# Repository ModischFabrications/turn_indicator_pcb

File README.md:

# turn_indicator_pcb

This is the PCB for [Turn Indicator](https://github.com/ModischFabrications/Turn_Indicator).

Open like regular in KiCad. Look into the docs zip under [Actions/KiCad Exports](https://github.com/ModischFabrications/turn_indicator_pcb/actions/workflows/exports.yml) to see renderings. 

This schematic is meant to be soldered manually onto a perfboard, but feel free to order a PCB instead. 

## Decisions

Size is determined by a generic 4x6 cm perfboard. 

### Electrical
Button panel connectors are grouped in pairs of 4 because my JST-XH set only has 2..5 pins. 
Grouping by input/output was the obvious choice,even if they are crossed at the buttons. 

Supply is a 18650 in a supply board, which means that grounding is useless. Using the bicylce frame as common ground could have been simple, but it's not worth the risk if there are 4+ wires routed anyways. 

Short-circuit-resistance of the power leads is archieved using a polyfuse. Resistance of the inputs is build-in, as they are high impedance, but the outputs are at risk. 

Introducing series resistances into every single connection could have made it safer, but I can't be arsed at the moment. Active-Low or High doesn't really matter either, a cross between adjacent leads would result in one overloading regardless. Feel free to insert ~300 ohm everywhere if you want to be safe. 

Sharing Clocks for the LED-stripes is technically possible, but a lot more work. Separate Pins, as seen here, is way easier.

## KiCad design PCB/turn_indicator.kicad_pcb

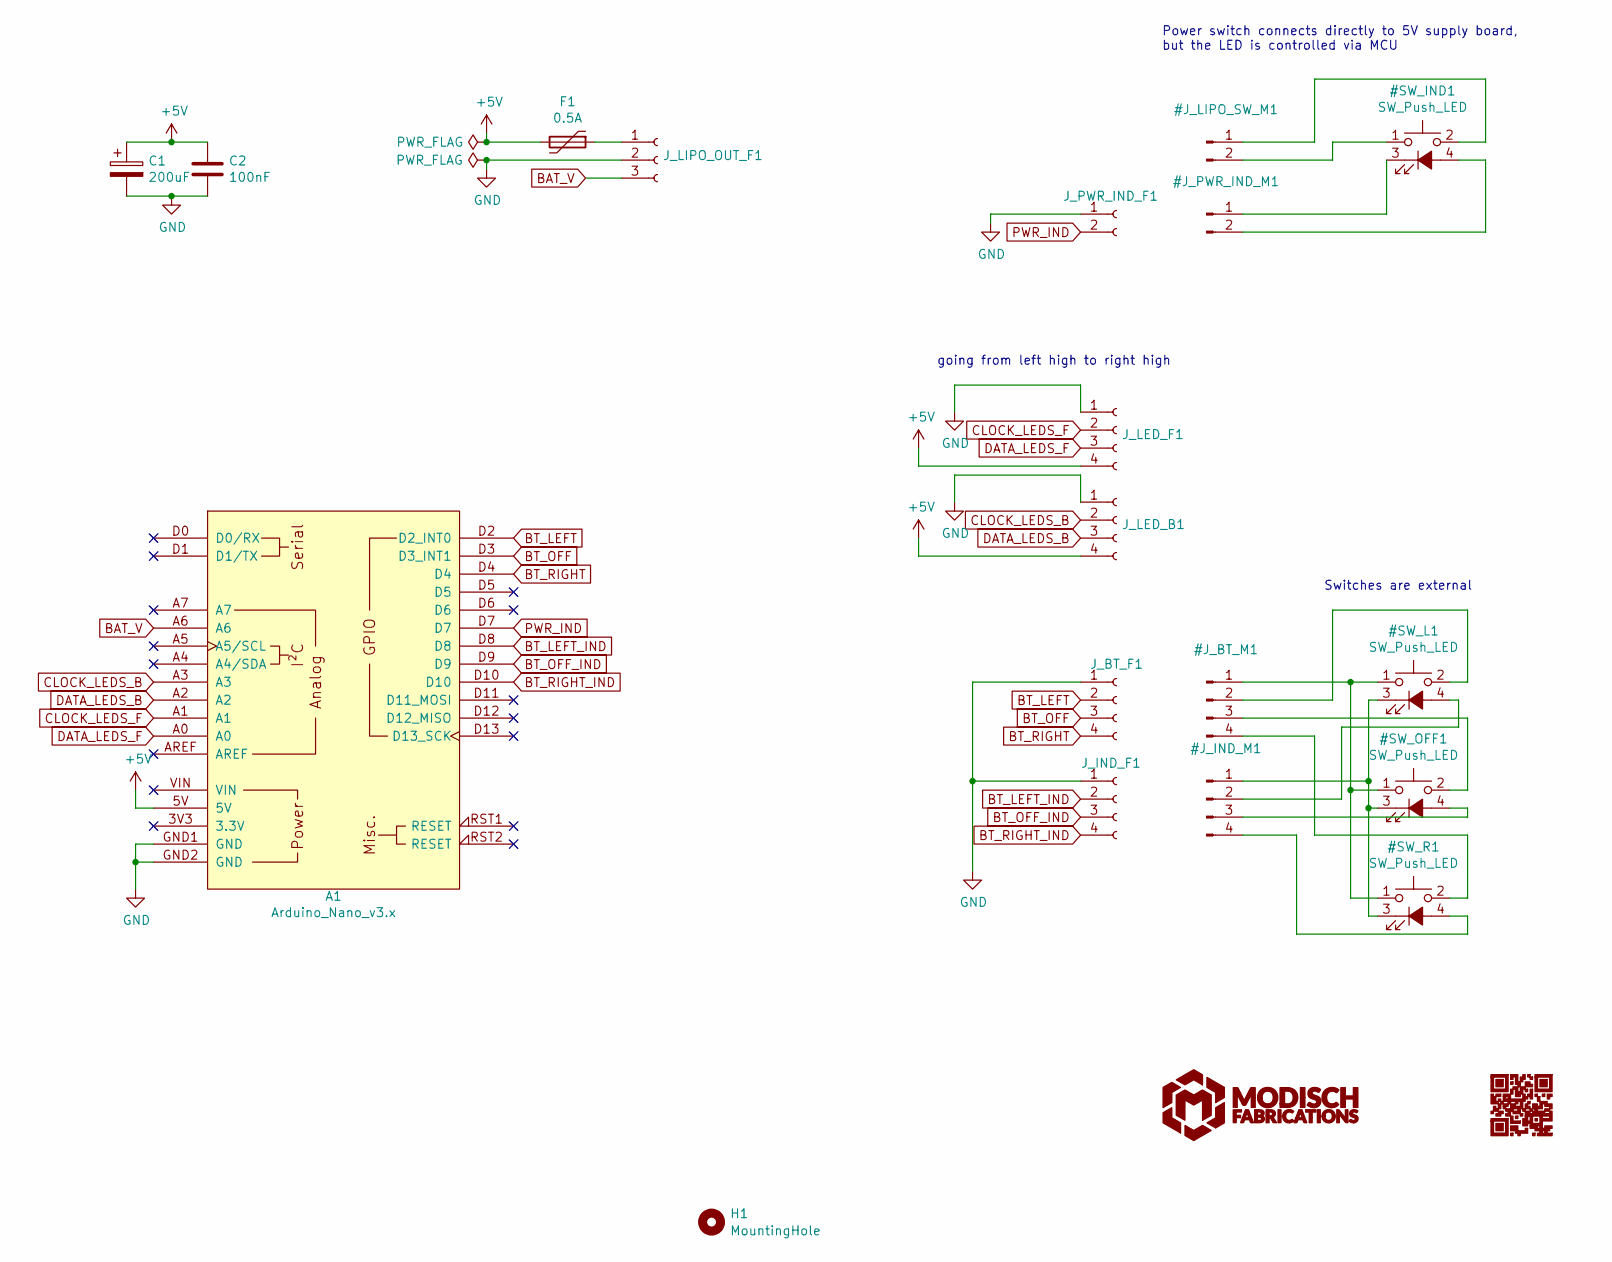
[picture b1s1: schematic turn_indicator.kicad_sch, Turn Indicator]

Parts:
A1: Arduino_Nano_v3.x; Arduino_Nano_Socket
C1: 200uF; CP_Radial_D8.0mm_P2.50mm
C2: 100nF; C_0603_1608Metric
F1: 0.5A; Fuse_1206_3216Metric_Pad1.42x1.75mm_HandSolder
H1: MountingHole; MountingHole_3.2mm_M3
J_BT_F1: Conn_01x04_Socket; JST_XH_B4B-XH-A_1x04_P2.50mm_Vertical
J_IND_F1: Conn_01x04_Socket; JST_XH_B4B-XH-A_1x04_P2.50mm_Vertical
J_LED_B1: Conn_01x04_Socket; JST_XH_B4B-XH-A_1x04_P2.50mm_Vertical
J_LED_F1: Conn_01x04_Socket; JST_XH_B4B-XH-A_1x04_P2.50mm_Vertical
J_LIPO_OUT_F1: Conn_01x03_Socket; JST_XH_B3B-XH-A_1x03_P2.50mm_Vertical
J_PWR_IND_F1: Conn_01x02_Socket; JST_XH_B2B-XH-A_1x02_P2.50mm_Vertical

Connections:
+5V: A1.5V, C1.1, C2.1, F1.2, J_LED_B1.4, J_LED_F1.4
BAT_V: A1.A6, J_LIPO_OUT_F1.3
BT_LEFT: A1.D2 (D2_INT0), J_BT_F1.2
BT_LEFT_IND: A1.D8, J_IND_F1.2
BT_OFF: A1.D3 (D3_INT1), J_BT_F1.3
BT_OFF_IND: A1.D9, J_IND_F1.3
BT_RIGHT: A1.D4, J_BT_F1.4
BT_RIGHT_IND: A1.D10, J_IND_F1.4
CLOCK_LEDS_B: A1.A3, J_LED_B1.2
CLOCK_LEDS_F: A1.A1, J_LED_F1.2
DATA_LEDS_B: A1.A2, J_LED_B1.3
DATA_LEDS_F: A1.A0, J_LED_F1.3
GND: A1.GND1 (GND), A1.GND2 (GND), C1.2, C2.2, J_BT_F1.1, J_IND_F1.1, J_LED_B1.1, J_LED_F1.1, J_LIPO_OUT_F1.2, J_PWR_IND_F1.1
unnamed: F1.1, J_LIPO_OUT_F1.1
PWR_IND: A1.D7, J_PWR_IND_F1.2

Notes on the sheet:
going from left high to right high
Switches are external
Power switch connects directly to 5V supply board, but the LED is controlled via MCU

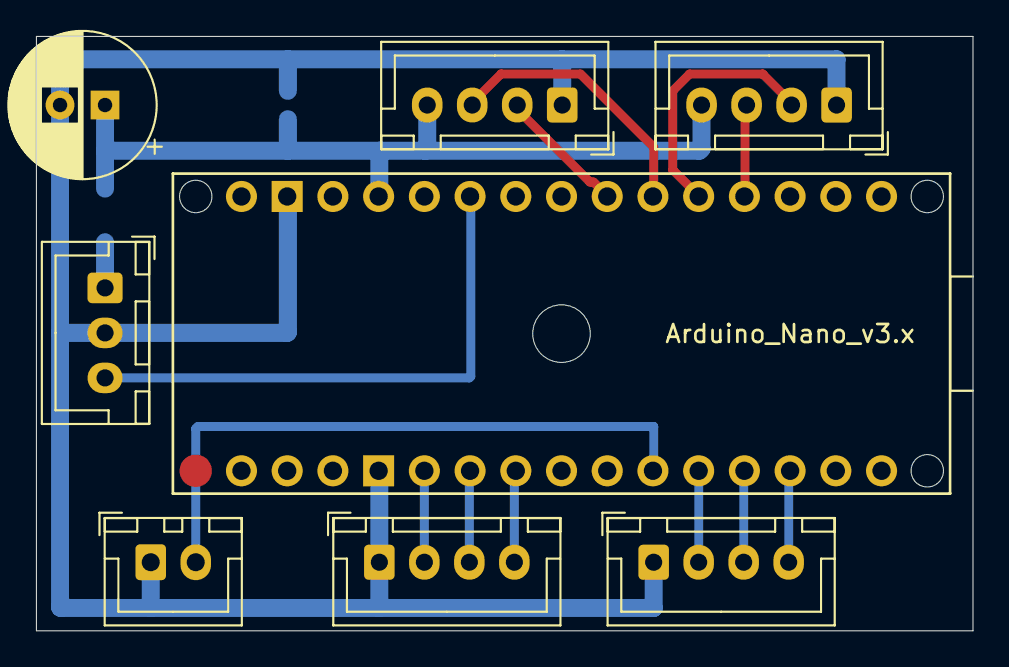
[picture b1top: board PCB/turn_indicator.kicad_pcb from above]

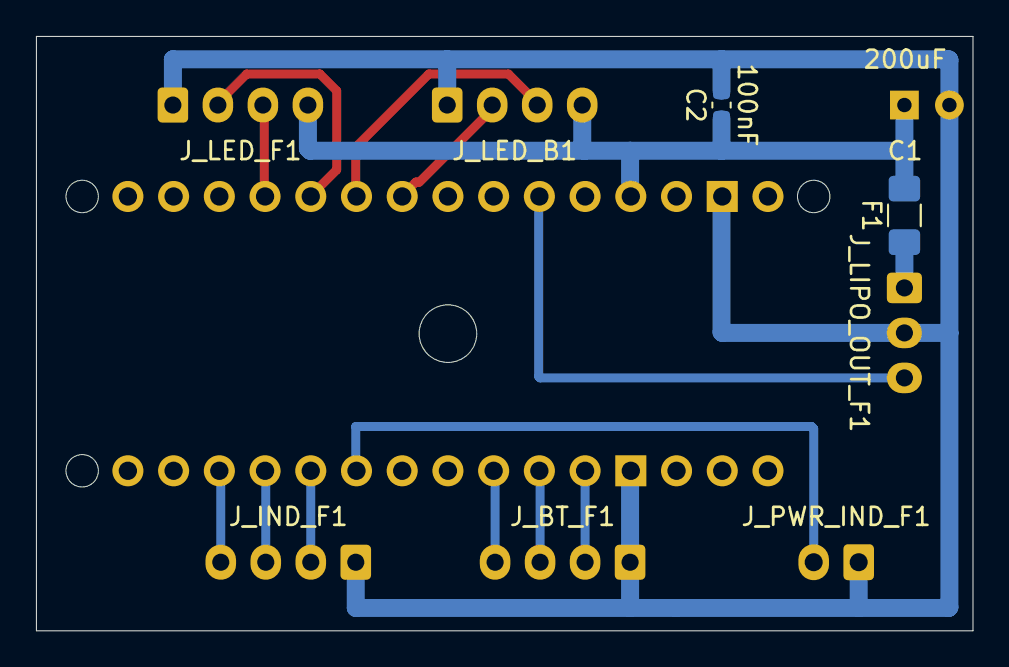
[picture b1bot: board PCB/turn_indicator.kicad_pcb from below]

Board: 2 copper layers, 52.0 x 33.0 mm, 11 parts (2 on the bottom side), 15 nets.

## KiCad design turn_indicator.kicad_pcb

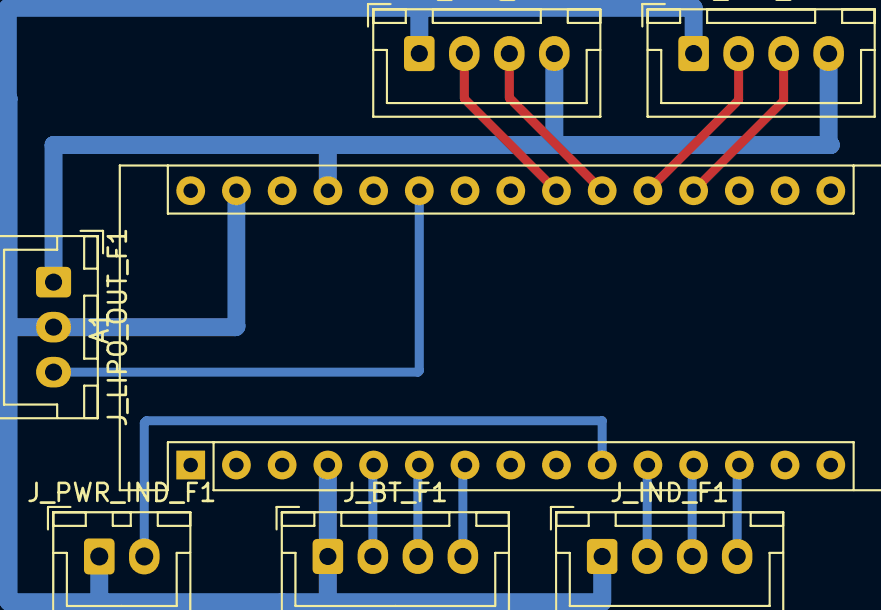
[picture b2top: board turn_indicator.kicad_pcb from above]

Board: 2 copper layers, 7 parts (0 on the bottom side), 14 nets.

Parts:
A1: Arduino_Nano_v3.x; Arduino_Nano
J_BT_F1: Conn_01x04_Female; JST_XH_B4B-XH-A_1x04_P2.50mm_Vertical
J_IND_F1: Conn_01x04_Female; JST_XH_B4B-XH-A_1x04_P2.50mm_Vertical
J_LED_L1: Conn_01x04_Female; JST_XH_B4B-XH-A_1x04_P2.50mm_Vertical
J_LED_R1: Conn_01x04_Female; JST_XH_B4B-XH-A_1x04_P2.50mm_Vertical
J_LIPO_OUT_F1: Conn_01x03_Female; JST_XH_B3B-XH-A_1x03_P2.50mm_Vertical
J_PWR_IND_F1: Conn_01x02_Female; JST_XH_B2B-XH-A_1x02_P2.50mm_Vertical

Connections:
+5V: A1.27, J_LED_L1.4, J_LED_R1.4, J_LIPO_OUT_F1.1
BAT_V: A1.25, J_LIPO_OUT_F1.3
BT_L: A1.5, J_BT_F1.2
BT_L_IND: A1.11, J_IND_F1.2
BT_OFF: A1.6, J_BT_F1.3
BT_OFF_IND: A1.12, J_IND_F1.3
BT_RIGHT: A1.7, J_BT_F1.4
BT_RIGHT_IND: A1.13, J_IND_F1.4
CLOCK_LEDS_L: A1.20, J_LED_L1.2
CLOCK_LEDS_R: A1.22, J_LED_R1.2
DATA_LEDS_L: A1.19, J_LED_L1.3
DATA_LEDS_R: A1.21, J_LED_R1.3
GND: A1.4, A1.29, J_BT_F1.1, J_IND_F1.1, J_LED_L1.1, J_LED_R1.1, J_LIPO_OUT_F1.2, J_PWR_IND_F1.1
PWR_IND: A1.10, J_PWR_IND_F1.2

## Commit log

2021-01-26 init and v1
2021-08-11 pcb subfolder and unknown pending changes
2021-08-11 shrink to 5x7 perfboard, add comments, add fuse and capacitors
2021-08-11 move export config
2021-08-11 fix export with file glob
2021-08-11 push always, use static paths
2021-08-11 check more, skip ogv upload, remove comments
2021-08-26 refine autobuild
2023-10-22 migrate to kicad 6, add gh actions from easylight
2023-10-22 update to kicad 7, increase fuse size to proper 1206, cleanup PCB, include QR code and MF logo
2023-10-22 remove migration cache, allow DRC to fail
2023-10-22 remove made up option, disable DRC instead
2023-10-22 fix very outdated style definition, based on https://github.com/INTI-CMNB/KiBot/issues/424#issuecomment-1510326910
